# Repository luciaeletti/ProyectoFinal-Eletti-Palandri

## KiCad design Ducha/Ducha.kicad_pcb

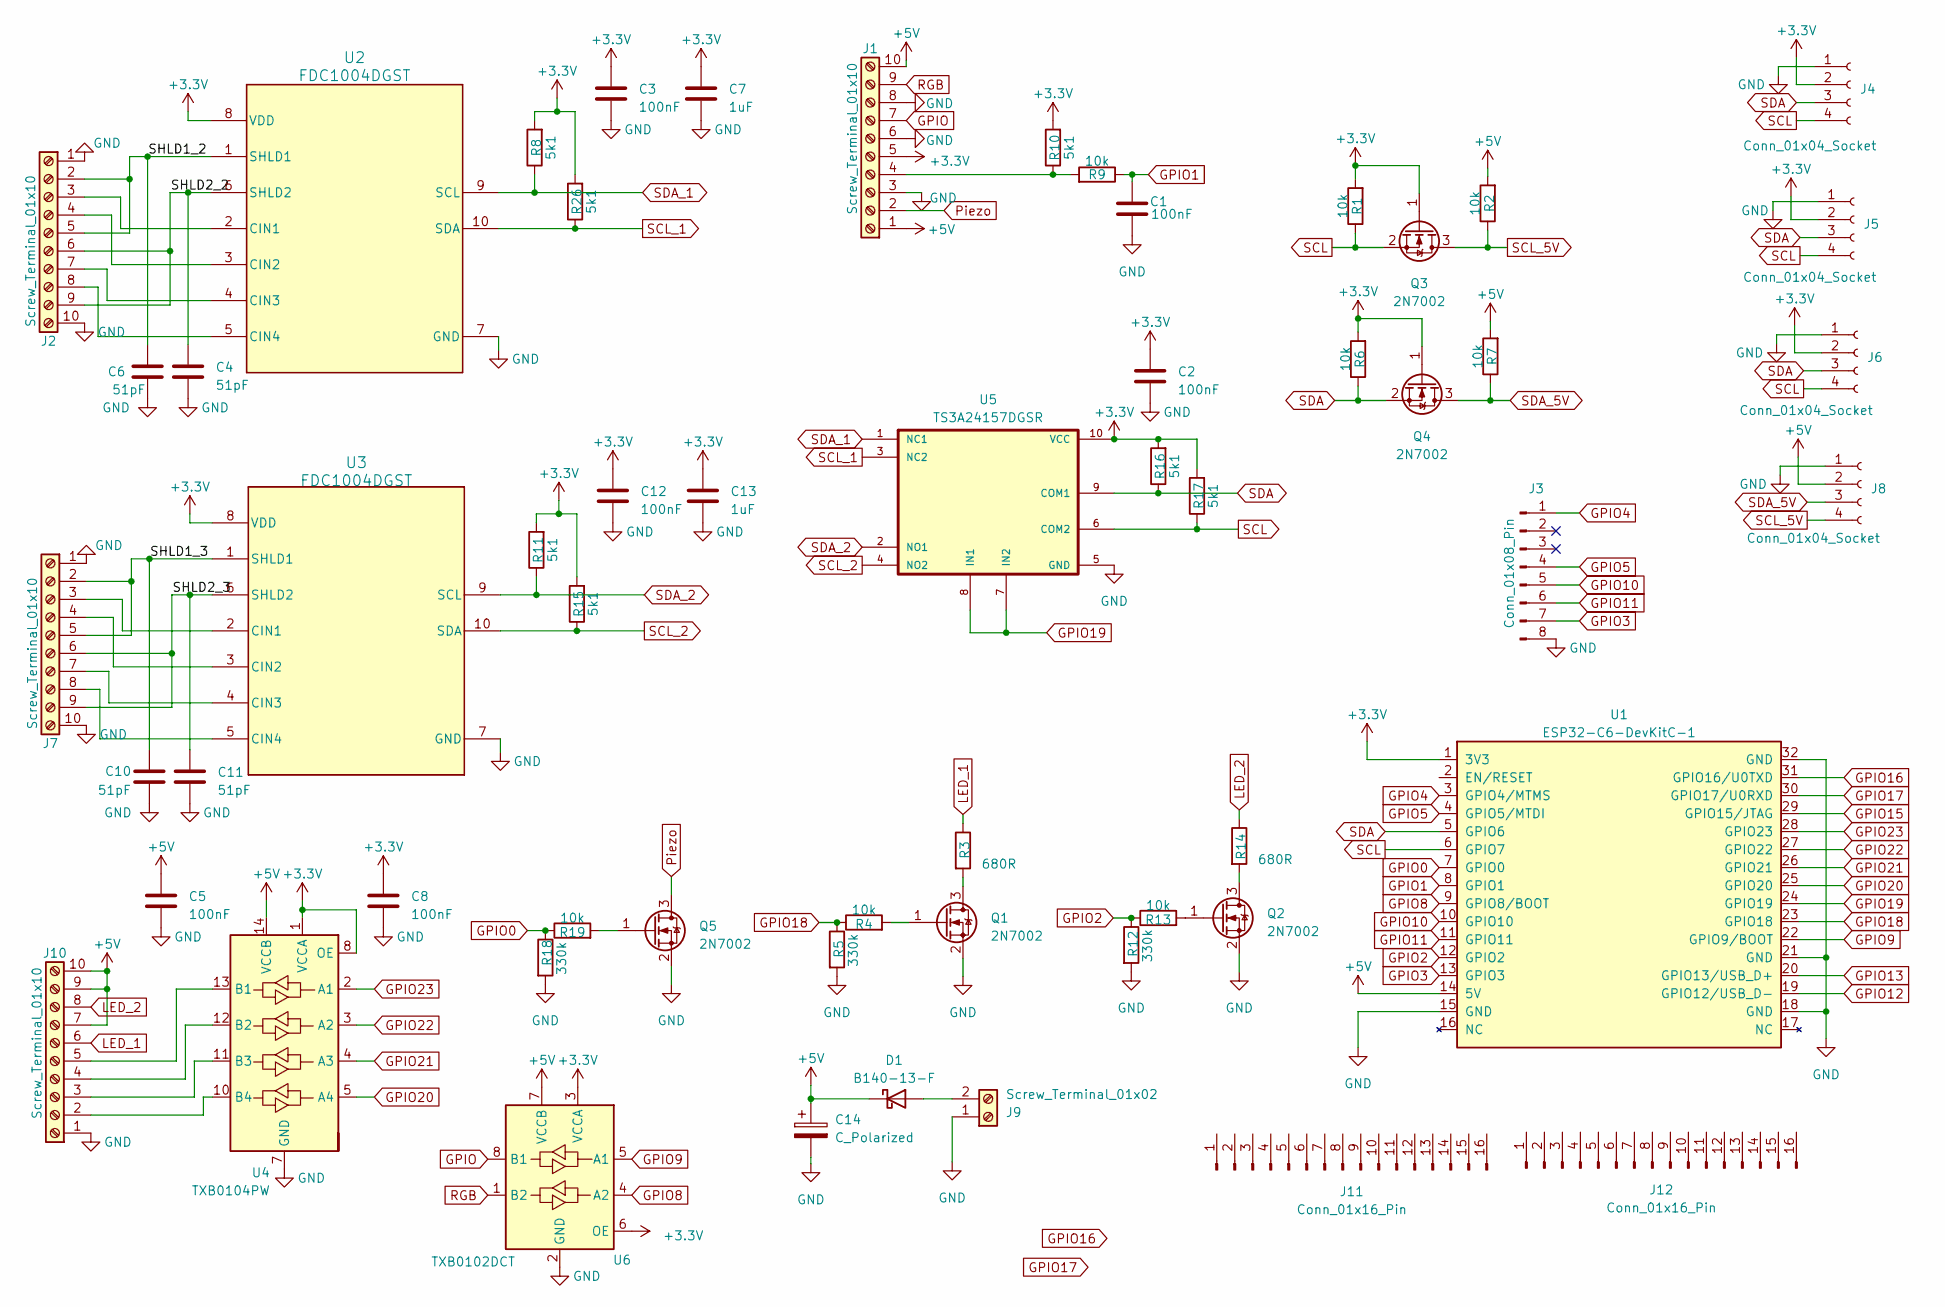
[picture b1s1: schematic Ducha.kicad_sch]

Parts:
C1, C2, C3, C5, C8, C12: 100nF; C_0603_1608Metric; Digikey Part Number 311-1343-1-ND
C4, C6, C10, C11: 51pF; C_0603_1608Metric; Digikey Part Number 311-3358-1-ND
C7, C13: 1uF; C_0603_1608Metric; Digikey Part Number 587-1242-1-ND
C14: C_Polarized; CP_Radial_D10.0mm_P5.00mm; Digikey Part Number 493-6095-1-ND
D1: B140-13-F; D_SMA; Digikey Part Number B140-FDICT-ND
J1, J2, J7, J10: Screw_Terminal_01x10; CONN_OSTVN10A150_OST; Digikey Part Number ED10567-ND
J3: Conn_01x08_Pin; PinHeader_1x08_P2.54mm_Horizontal; Digikey Part Number A106934-ND
J4, J5, J6, J8: Conn_01x04_Socket; PinHeader_1x04_P2.54mm_Vertical; Digikey Part Number WM4202-ND
J9: Screw_Terminal_01x02; TerminalBlock_bornier-2_P5.08mm; Digikey Part Number 732-10955-ND
J11, J12: Conn_01x16_Pin; Digikey Part Number 61301611821-ND
Q1, Q2, Q3, Q4, Q5: 2N7002; SOT-23; Digikey Part Number 4878-2N7002CT-ND
R1, R2, R4, R6, R7, R9, R13, R19: 10k; R_0603_1608Metric; Digikey Part Number 311-10KGRCT-ND
R3, R14: 680R; R_0603_1608Metric; Digikey Part Number 311-680GRCT-ND
R5, R12, R18: 330k; R_0603_1608Metric; Digikey Part Number 311-330KGRCT-ND
R8, R10, R11, R15, R16, R17, R26: 5k1; R_0603_1608Metric; Digikey Part Number 311-5.1KGRCT-ND
U1: ESP32-C6-DevKitC-1; Digikey Part Number 1965-ESP32-C6-DEVKITC-1-N8-ND
U2, U3: FDC1004DGST; DGS0010A_N; Digikey Part Number 296-49639-1-ND
U4: TXB0104PW; TSSOP-14_4.4x5mm_P0.65mm; Digikey Part Number 296-21929-1-ND
U5: TS3A24157DGSR; SOP50P490X110-10N; Digikey Part Number 296-22856-1-ND
U6: TXB0102DCT; SOP50P310X90-8N; Digikey Part Number 296-22862-1-ND

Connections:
+3.3V: C2.1, C3.1, C7.1, C8.1, C12.1, C13.1, J1.5, J4.2, J5.2, J6.2, Q3.1 (G), Q4.1 (G), R1.2, R6.2, R8.2, R10.2, R11.2, R15.2, R16.2, R17.2, R26.2, U1.1 (3V3), U2.8 (VDD), U3.8 (VDD), U4.1 (VCCA), U4.8 (OE), U5.10 (VCC), U6.3 (VCCA), U6.6 (OE)
+5V: C5.1, C14.1, D1.1 (K), J1.1, J1.10, J8.2, J10.7, J10.9, J10.10, R2.2, R7.2, U1.14 (5V), U4.14 (VCCB), U6.7 (VCCB)
/SHLD1_2: C6.1, J2.2, J2.5, U2.1 (SHLD1)
/SHLD1_3: C10.1, J7.2, J7.5, U3.1 (SHLD1)
/SHLD2_2: C4.1, J2.6, J2.9, U2.6 (SHLD2)
/SHLD2_3: C11.1, J7.6, J7.9, U3.6 (SHLD2)
GND: C1.2, C2.2, C3.2, C4.2, C5.2, C6.2, C7.2, C8.2, C10.2, C11.2, C12.2, C13.2, C14.2, J1.3, J1.6, J1.8, J2.1, J2.10, J3.8, J4.1, J5.1, J6.1, J7.1, J7.10, J8.1, J9.1, J10.1, Q1.2 (S), Q2.2 (S), Q5.2 (S), R5.2, R12.2, R18.2, U1.15 (GND), U1.18 (GND), U1.21 (GND), U1.32 (GND), U2.7 (GND), U3.7 (GND), U4.7 (GND), U5.5 (GND), U6.2 (GND)
GPIO: J1.7, U6.8 (B1)
GPIO0: R18.1, R19.1, U1.7 (GPIO0)
GPIO1: C1.1, R9.1, U1.8 (GPIO1)
GPIO2: R12.1, R13.1, U1.12 (GPIO2)
GPIO3: J3.7, U1.13 (GPIO3)
GPIO4: J3.1, U1.3 (GPIO4/MTMS)
GPIO5: J3.4, U1.4 (GPIO5/MTDI)
GPIO8: U1.9 (GPIO8/BOOT), U6.4 (A2)
GPIO9: U1.22 (GPIO9/BOOT), U6.5 (A1)
GPIO10: J3.5, U1.10 (GPIO10)
GPIO11: J3.6, U1.11 (GPIO11)
GPIO12: U1.19 (GPIO12/USB_D-)
GPIO13: U1.20 (GPIO13/USB_D+)
GPIO15: U1.29 (GPIO15/JTAG)
GPIO16: U1.31 (GPIO16/U0TXD)
GPIO17: U1.30 (GPIO17/U0RXD)
GPIO18: R4.1, R5.1, U1.23 (GPIO18)
GPIO19: U1.24 (GPIO19), U5.7 (IN2), U5.8 (IN1)
GPIO20: U1.25 (GPIO20), U4.5 (A4)
GPIO21: U1.26 (GPIO21), U4.4 (A3)
GPIO22: U1.27 (GPIO22), U4.3 (A2)
GPIO23: U1.28 (GPIO23), U4.2 (A1)
LED_1: J10.6, R3.1
LED_2: J10.8, R14.1
unnamed: D1.2 (A), J9.2
unnamed: J1.4, R9.2, R10.1
unnamed: J2.3, U2.2 (CIN1)
unnamed: J2.4, U2.3 (CIN2)
unnamed: J2.7, U2.4 (CIN3)
unnamed: J2.8, U2.5 (CIN4)
unnamed: J7.3, U3.2 (CIN1)
unnamed: J7.4, U3.3 (CIN2)
unnamed: J7.7, U3.4 (CIN3)
unnamed: J7.8, U3.5 (CIN4)
unnamed: J10.2, U4.10 (B4)
unnamed: J10.3, U4.11 (B3)
unnamed: J10.4, U4.12 (B2)
unnamed: J10.5, U4.13 (B1)
unnamed: Q1.3 (D), R3.2
unnamed: Q1.1 (G), R4.2
unnamed: Q2.3 (D), R14.2
unnamed: Q2.1 (G), R13.2
unnamed: Q5.1 (G), R19.2
Piezo: J1.2, Q5.3 (D)
RGB: J1.9, U6.1 (B2)
SCL: J4.4, J5.4, J6.4, Q3.2 (S), R1.1, R17.1, U1.6 (GPIO7), U5.6 (COM2)
SCL_1: R26.1, U2.10 (SDA), U5.3 (NC2)
SCL_2: R15.1, U3.10 (SDA), U5.4 (NO2)
SCL_5V: J8.4, Q3.3 (D), R2.1
SDA: J4.3, J5.3, J6.3, Q4.2 (S), R6.1, R16.1, U1.5 (GPIO6), U5.9 (COM1)
SDA_1: R8.1, U2.9 (SCL), U5.1 (NC1)
SDA_2: R11.1, U3.9 (SCL), U5.2 (NO1)
SDA_5V: J8.3, Q4.3 (D), R7.1

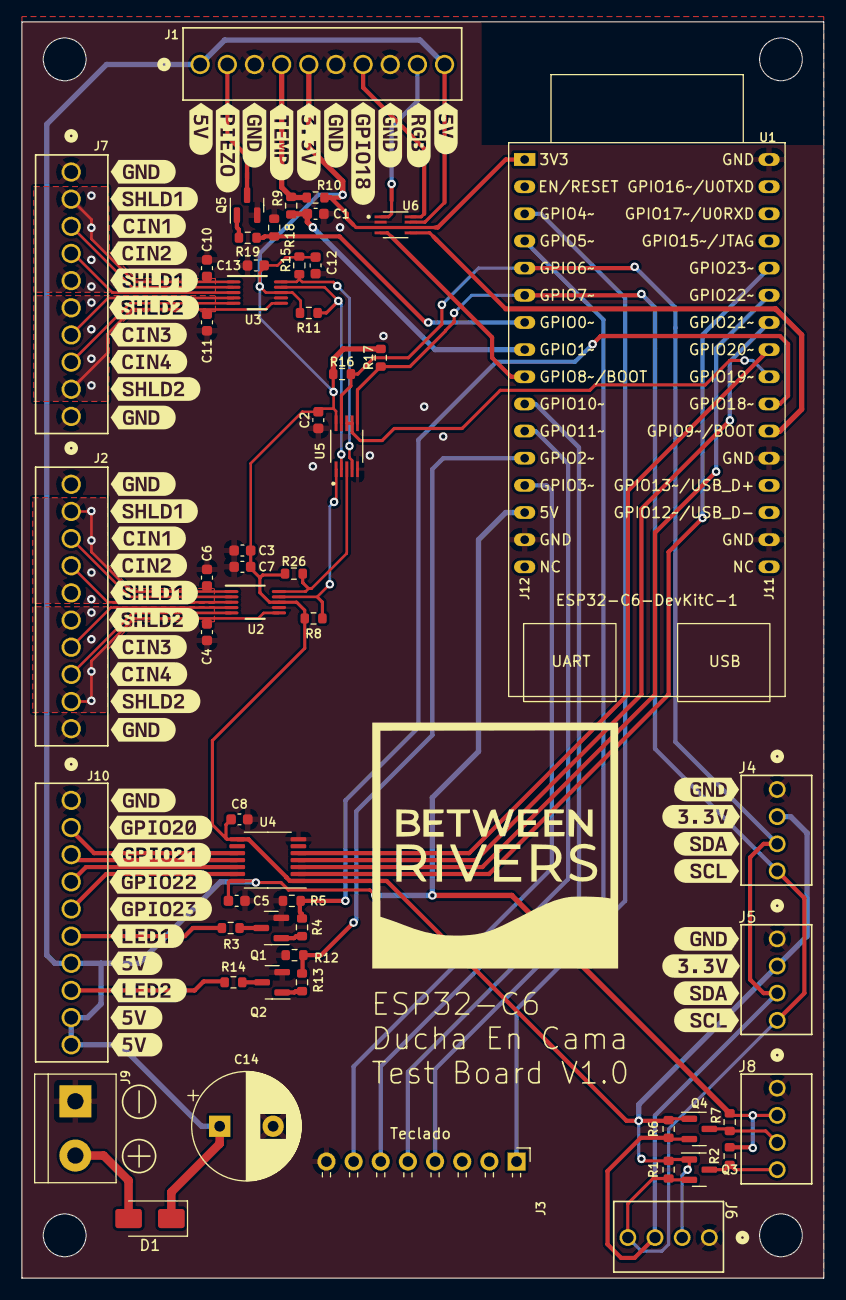
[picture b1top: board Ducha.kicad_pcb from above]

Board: 2 copper layers, 75.0 x 117.5 mm, 103 parts (0 on the bottom side), 55 nets.

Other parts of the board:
kibuzzard-65B00E41: G***; kibuzzard-65B00E41
kibuzzard-65B001B5, kibuzzard-65B001B5#2, kibuzzard-65B001B5#3, kibuzzard-65B001B5#4, kibuzzard-65B001B5#5: G***; kibuzzard-65B001B5
kibuzzard-65B001BD: G***; kibuzzard-65B001BD
kibuzzard-65B001C6, kibuzzard-65B001C6#2, kibuzzard-65B001C6#3, kibuzzard-65B001C6#4, kibuzzard-65B001C6#5, kibuzzard-65B001C6#6, kibuzzard-65B001C6#7, kibuzzard-65B001C6#8: G***; kibuzzard-65B001C6
kibuzzard-65B002B4, kibuzzard-65B002B4#2, kibuzzard-65B002B4#3, kibuzzard-65B002B4#4: G***; kibuzzard-65B002B4
kibuzzard-65B002CD, kibuzzard-65B002CD#2: G***; kibuzzard-65B002CD
kibuzzard-65B002E1, kibuzzard-65B002E1#2: G***; kibuzzard-65B002E1
kibuzzard-65B003BA: G***; kibuzzard-65B003BA
kibuzzard-65B003C5: G***; kibuzzard-65B003C5
kibuzzard-65B003CB: G***; kibuzzard-65B003CB
kibuzzard-65B0025A, kibuzzard-65B0025A#2, kibuzzard-65B0025A#3, kibuzzard-65B0025A#4: G***; kibuzzard-65B0025A
kibuzzard-65B0029D, kibuzzard-65B0029D#2: G***; kibuzzard-65B0029D
kibuzzard-65B0038A: G***; kibuzzard-65B0038A
kibuzzard-65B115E3: G***; kibuzzard-65B115E3
kibuzzard-65B115EB: G***; kibuzzard-65B115EB
kibuzzard-65B115FA: G***; kibuzzard-65B115FA
kibuzzard-65B133D2, kibuzzard-65B133D2#2: G***; kibuzzard-65B133D2
kibuzzard-65B133EB, kibuzzard-65B133EB#2: G***; kibuzzard-65B133EB
kibuzzard-65B133F1, kibuzzard-65B133F1#2: G***; kibuzzard-65B133F1
kibuzzard-65B133F5, kibuzzard-65B133F5#2: G***; kibuzzard-65B133F5
kibuzzard-65B00279, kibuzzard-65B00279#2: G***; kibuzzard-65B00279
kibuzzard-65B00352: G***; kibuzzard-65B00352
kibuzzard-65B00375: G***; kibuzzard-65B00375

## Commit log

2024-04-15 Se sube firmware del equipo
2024-04-15 Se suben ejemplos
2024-04-15 Se suben modificaciones del firmware
2024-04-16 Se suben avances del firmware de Ducha en Cama
2024-04-17 Se suben modificaciones de firmware
2024-04-18 Otras modificaciones de firmware
2024-04-19 Se cargan avances en el firmware: wifi y mqtt
2024-04-24 Se sube firmware modificado: conexión a wifi por ESPTouch
2024-04-25 Se sube modificaciones de firmware: tareas sobre wifi y mqtt
2024-04-26 Se suben archivos de hardware
2024-04-29 Extras
2024-04-30 Se sube codigo con la tarea de WIFI arreglada
2024-05-02 Se suben modificaciones: i2c
2024-05-14 Se sube firmware modificado: driver de RTC agregado
2024-05-16 Se sube modificaciones en la tarea de adquisicion
2024-05-17 Tarea de adquisicion de datos funcionando
2024-05-24 Se suben ultimas modificaciones: tarea WIFI y MQTT
2024-05-27 Se carga driver at24c32
2024-06-03 Se sube nuevo archivo a modules: control
2024-06-04 Se suben modificaciones: cambios en Control y Conexión
2024-06-06 Conexion a wifi exitosa
2024-06-07 Se suben modificaciones en conexion WIFI
2024-06-11 Se sube driver rtc modificado
2024-06-13 Se agrega en data un archivo con todas las definiciones
2024-06-13 Se modifica driver at24c
2024-06-14 TRabajo con la bomba de ducha
2024-06-14 Se sube nuevo archivo STORE
2024-06-18 se sube nuevo archivo a modules
2024-06-18 Actualizacion de archivo Store: se agregan funciones de lectura
2024-06-19 Se sube archivo store modificado
2024-06-19 Se suben modificaciones en STORE
2024-06-24 Se suben avances
2024-07-01 Se agrega proceso Autolavado
2024-07-02 Modificaciones en menu
2024-07-02 Se suben avances del menu
2024-07-03 Avances sobre proceso autolavado
2024-08-01 Se sube version con proceso de ducha automatico
2024-08-07 Se sube proceso de ducha modificado y control de temperatura
2024-09-02 Se suben actualizaciones: modificacion en la lectura del teclado y control de temperatura
